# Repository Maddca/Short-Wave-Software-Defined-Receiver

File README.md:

# Short-Wave-Software-Defined-Receiver
The goal of this project has been to design a Software Defined Radio Receiver with [Taylor Smith](https://github.com/TaylorSmith28) for the Engineering Electronics II class.
## Design Objectives
For this project we were given the following design objectives by [Dr. Rob Frohne](https://github.com/frohro):

#### Objectives
 - Low noise figure
 - Good image rejection
 - Minimum discernible signal of less than 1uV
 - $25 Budget

For specifications we originally were going to have a narrow bandpass filter, but ended up switching to a relatively wider one in the later stages of the project.

#### Specifications
 - Frequency Range of 7-12MHz
 - Short Wave Radio
 - Uses a Tayloe Mixer
 - Uses a Multiple Feedback Lowpass Filter and Amplifier
 	- 25 V/V gain with Cutoff Frequency of more than 50KHz
 - Butterworth Bandpass Filter
 - Uses the Raspberry Pi Pico
 
 ## Overview
 The SDR receiver connects to an antenna and filters, mixes, and amplifies that signal to achieve the desired I and Q signals. The I and Q signals are then sent through an external sound card with a sample rate of 48kHz where software then handles the demodulation of the signal into audio. The mixer requires a 90 degree offset of two clocks operating at a frequency that can be controlled through software. In our design we use a Raspberry Pi Pico to control an si5351 to supply those two 90 degree offset clocks. There were some significant issues with this since the code supplied by professor Frohne didn't work when ported over to the Raspberry Pi Pico. In theory though the Raspberry Pi Pico interfaces with Quisk to tune to a certain frequency by adjusting the frequency of the si5351 clocks.
 
 ## Theory

The Block Diagram above shows the basics of how the SDR works. We get an input signal from the antenna which is passed through the bandpass filter and sent to the Tayloe Mixer that uses a 1:4 demultiplexer and low pass filters and ampliers to create the I and Q quardrature signals. After the demuiltiplexer creates 4 signals each 90 degrees out of phase with each other those signals are combined together to create the I and Q signals to be sent to the Audio Jack.

## Schematic Version 6

### Bandpass Filter

 Above is the bandpass filter made using the [LC Filter Design Tool](https://rf-tools.com/lc-filter/.). It is a 3rd order, conventional series first, Butterworth, bandpass filter that passes 7-12Mhz frequencies.
 
 ### Tayloe Mixer
 
The Tayloe Mixer above is comprised of the Demultiplexer stage which seperates the input signal into four signals all 90 degrees out of phase with each other. Then the signals that are 180 degrees out of phase with each other are combined in the following amplifier and low pass filter stage using opamps. The filter/amplifier here is a multiple feedback low pass filter and amplifier, in this case multiple refers to the filter being second order rather than single order.

### Voltage Smoother

The voltage smoother above simply uses varying capacitor sizes to lower the noise coming from the USB.

### Oscillator

The oscillator above is what outputs the clock signals necessary to run the Tayloe Mixer. It is controlled by the Raspberry Pi Pico on the SDA and SCL inputs.

### Raspberry Pi Pico

Above is the part of the schematic dealing with the Raspberry Pi Pico. The main thing of interest here is to note the pull up resistors and the GPIO pin the SDA and SCL are connected to, since the pin needs to be I2C compatible, in this case pins 6 and 7 or GPIO 4 and 5 are I2C compatible.

## Simulations
Simulations were for the most part conducted in [LTSpice](https://www.analog.com/en/design-center/design-tools-and-calculators/ltspice-simulator.html).
### Bandpass Filter Simulations

The Bandpass filter was designed to pass frequencies between 7 and 12 MHz, which is what the ac simulation shows.

### Lowpass Filter Simulations

## Issues
The first major issue we encountered was not having functional code because of the port over to Raspberry Pi Pico. It took 2 days of troubleshooting to get the appropriate clock signal to display and thats still without the ability to change frequencies, which currently causes the program to hang. The second major issue was much simpler. When we went to test our bandpass filter we came to the realization that one of the leads on the handwound inductors couldn't make a good connection because there was still enamel on it. After several failed attempts to remove it we decided jump the bandpass filter, but much later discovered that shorting the bandpass filter with a wire caused one of the resistors responsible for the dc offset to be in parallel with the resistor in the signal generator. This caused us to lose our DC Offset which caused the SDR not to work. To resolve this issue we simply shorted the bandpass filter with a capacitor.
## Results
We ended up with a minimum discernable signal of approx 1uV and when we tried the antenna we listened to some Catholic sermon on sunday.

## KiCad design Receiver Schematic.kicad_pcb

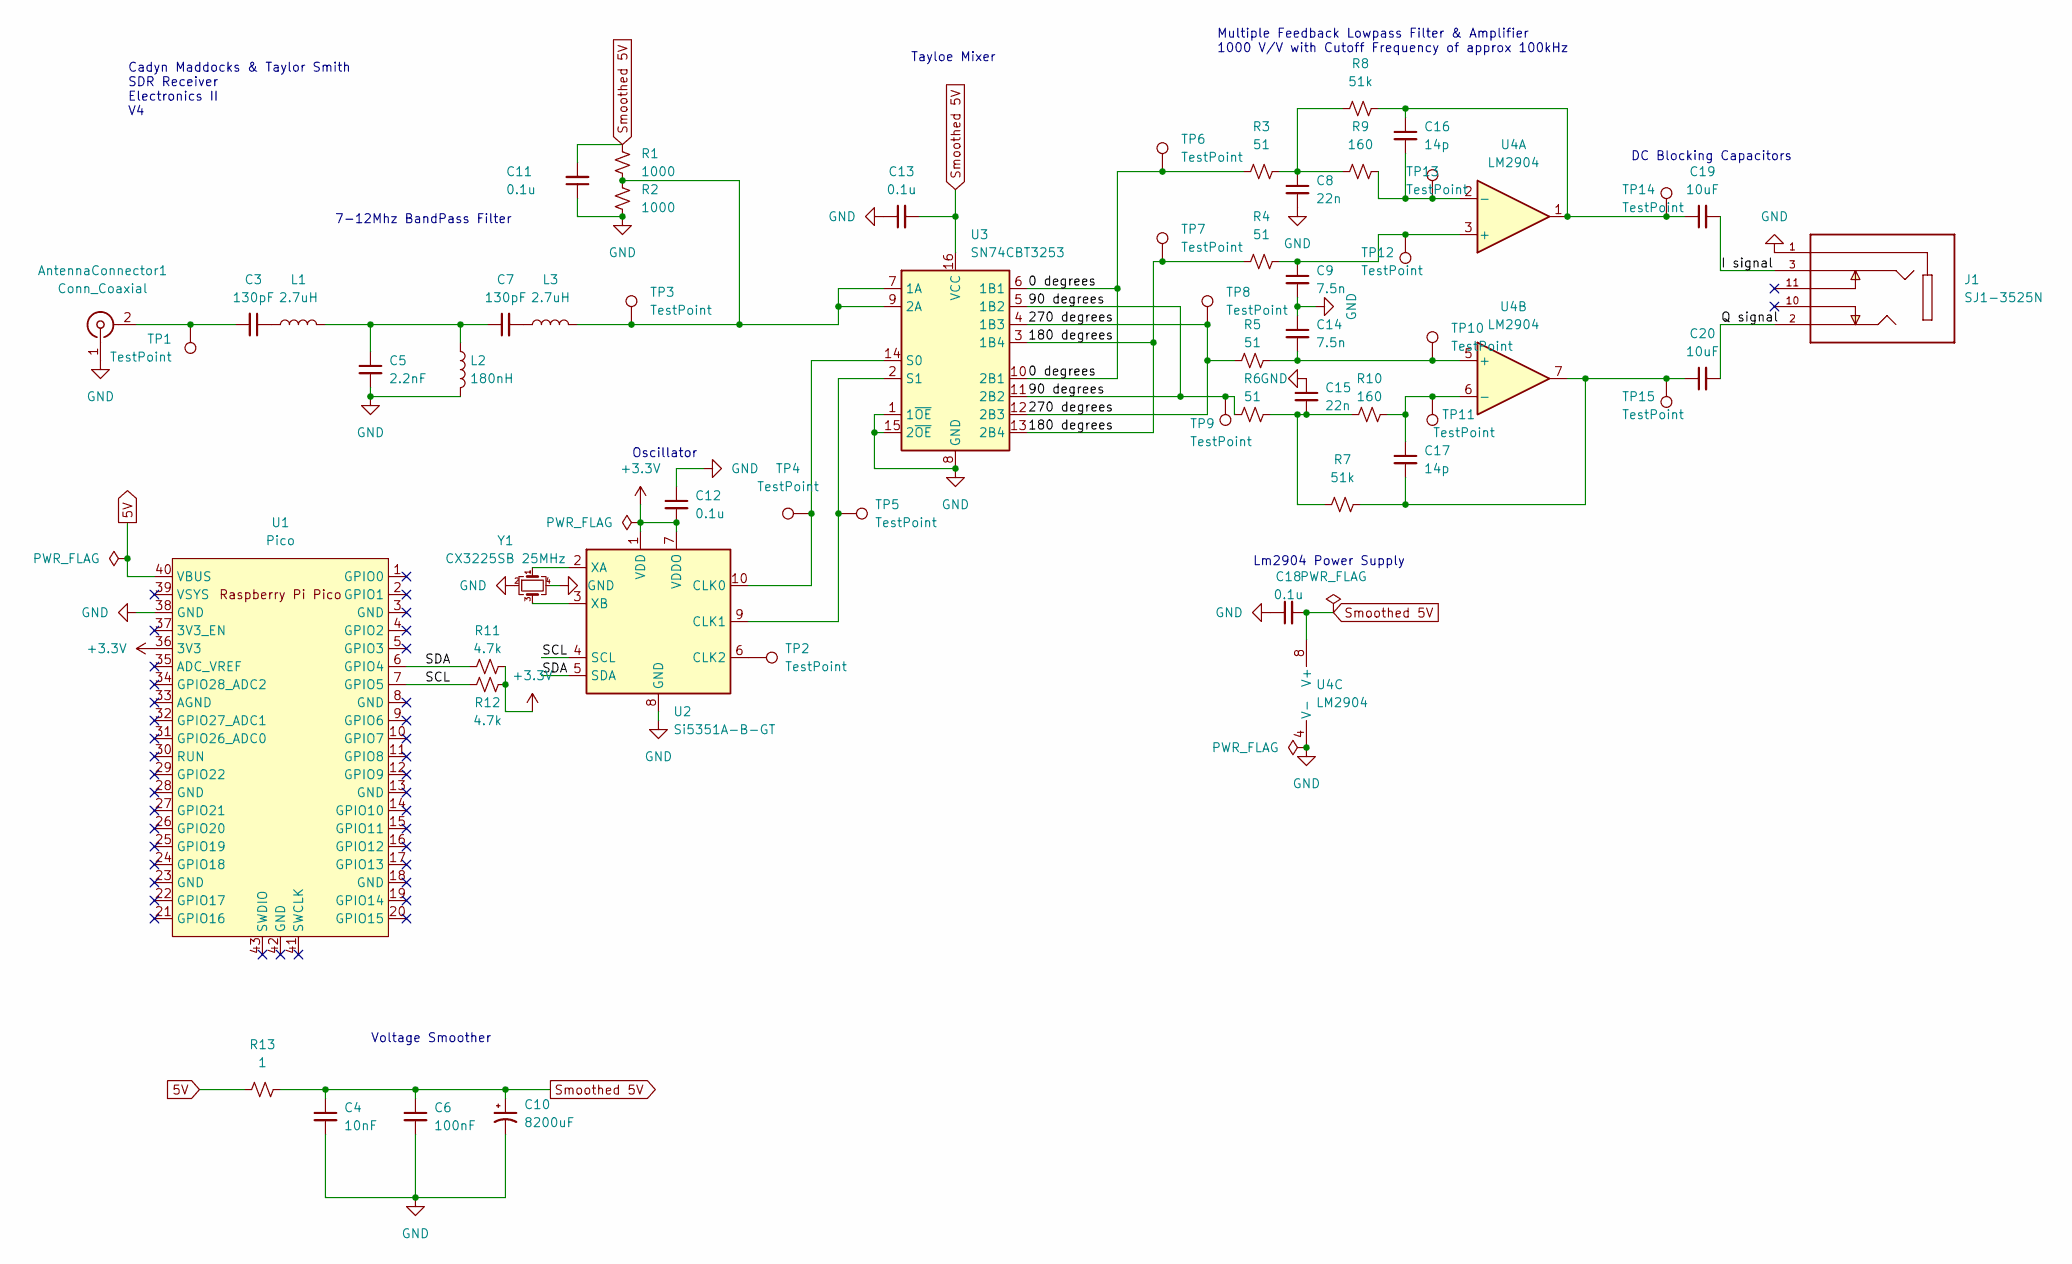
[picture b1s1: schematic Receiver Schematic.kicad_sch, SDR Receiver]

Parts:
AntennaConnector1: Conn_Coaxial; BNC_Amphenol_B6252HB-NPP3G-50_Horizontal
C3, C7: 130pF; C_0805_2012Metric
C4: 10nF; C_0805_2012Metric
C5: 2.2nF; C_0805_2012Metric
C6: 100nF; C_0805_2012Metric
C8, C15: 22n; C_0805_2012Metric
C9: 7.5n; C_0805_2012Metric
C10: 8200uF; CP_Radial_D16.0mm_P7.50mm
C11, C12, C13, C18: 0.1u; C_0805_2012Metric
C14: 7.5n; C_1206_3216Metric
C16, C17: 14p; C_0805_2012Metric
C19, C20: 10uF; C_0805_2012Metric
J1: SJ1-3525N; CUI_SJ1-3525N; PARTREV 1.02
L1, L3: 2.7uH; L_Toroid_Vertical_L10.0mm_W5.0mm_P5.08mm
L2: 180nH; L_Toroid_Vertical_L10.0mm_W5.0mm_P5.08mm
R1, R2: 1000; R_0805_2012Metric
R3, R4, R5, R6: 51; R_0805_2012Metric
R7, R8: 51k; R_0805_2012Metric
R9, R10: 160; R_0805_2012Metric
R11, R12: 4.7k; R_0805_2012Metric
R13: 1; R_0805_2012Metric
TP1, TP2, TP3, TP4, TP5, TP6, TP7, TP8, TP9, TP10, TP11, TP12, TP13, TP14, TP15: TestPoint; TestPoint_THTPad_2.0x2.0mm_Drill1.0mm
U1: Pico; RPi_Pico_SMD_TH
U2: Si5351A-B-GT; MSOP-10_3x3mm_P0.5mm
U3: SN74CBT3253; SOIC-16_3.9x9.9mm_P1.27mm
U4: LM2904; SOIC-8_3.9x4.9mm_P1.27mm
Y1: CX3225SB 25MHz; Crystal_SMD_TXC_7M-4Pin_3.2x2.5mm

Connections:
5V: R13.1, U1.40 (VBUS)
+3V3: C12.2, R11.2, R12.2, U1.36 (3V3), U2.1 (VDD), U2.7 (VDDO)
/0 degrees: R3.1, TP6.1, U3.6 (1B1), U3.10 (2B1)
/90 degrees: R6.1, TP9.1, U3.5 (1B2), U3.11 (2B2)
/180 degrees: R4.1, TP7.1, U3.3 (1B4), U3.13 (2B4)
/270 degrees: R5.1, TP8.1, U3.4 (1B3), U3.12 (2B3)
/I signal: C19.2, J1.3
/Q signal: C20.2, J1.2
/SCL: R12.1, U1.7 (GPIO5), U2.4 (SCL)
/SDA: R11.1, U1.6 (GPIO4), U2.5 (SDA)
GND: AntennaConnector1.1 (In), C4.2, C5.2, C6.2, C8.2, C9.2, C10.2, C11.1, C12.1, C13.1, C14.1, C15.1, C18.1, J1.1, L2.2, R2.2, U1.38 (GND), U2.8 (GND), U3.1 (1~OE), U3.8 (GND), U3.15 (2~OE), U4.4 (V-), Y1.2, Y1.4
unnamed: AntennaConnector1.2 (Ext), C3.2, TP1.1
unnamed: C3.1, L1.1
unnamed: C5.1, C7.1, L1.2, L2.1
unnamed: C7.2, L3.1
unnamed: C8.1, R3.2, R8.1, R9.1
unnamed: C9.1, R4.2, TP12.1, U4.3 (+)
unnamed: C14.2, R5.2, TP10.1, U4.5 (+)
unnamed: C15.2, R6.2, R7.1, R10.1
unnamed: C16.1, C19.1, R8.2, TP14.1, U4.1
unnamed: C16.2, R9.2, TP13.1, U4.2 (-)
unnamed: C17.1, R10.2, TP11.1, U4.6 (-)
unnamed: C17.2, C20.1, R7.2, TP15.1, U4.7
unnamed: L3.2, R1.2, R2.1, TP3.1, U3.7 (1A), U3.9 (2A)
unnamed: TP2.1, U2.6 (CLK2)
unnamed: TP4.1, U2.10 (CLK0), U3.14 (S0)
unnamed: TP5.1, U2.9 (CLK1), U3.2 (S1)
unnamed: U2.2 (XA), Y1.1
unnamed: U2.3 (XB), Y1.3
Smoothed 5V: C4.1, C6.1, C10.1, C11.2, C13.2, C18.2, R1.1, R13.2, U3.16 (VCC), U4.8 (V+)

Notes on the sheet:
Multiple Feedback Lowpass Filter & Amplifier 1000 V/V with Cutoff Frequency of approx 100kHz
Oscillator
Lm2904 Power Supply
Tayloe Mixer
7-12Mhz BandPass Filter
DC Blocking Capacitors
Voltage Smoother
Cadyn Maddocks & Taylor Smith SDR Receiver Electronics II V4

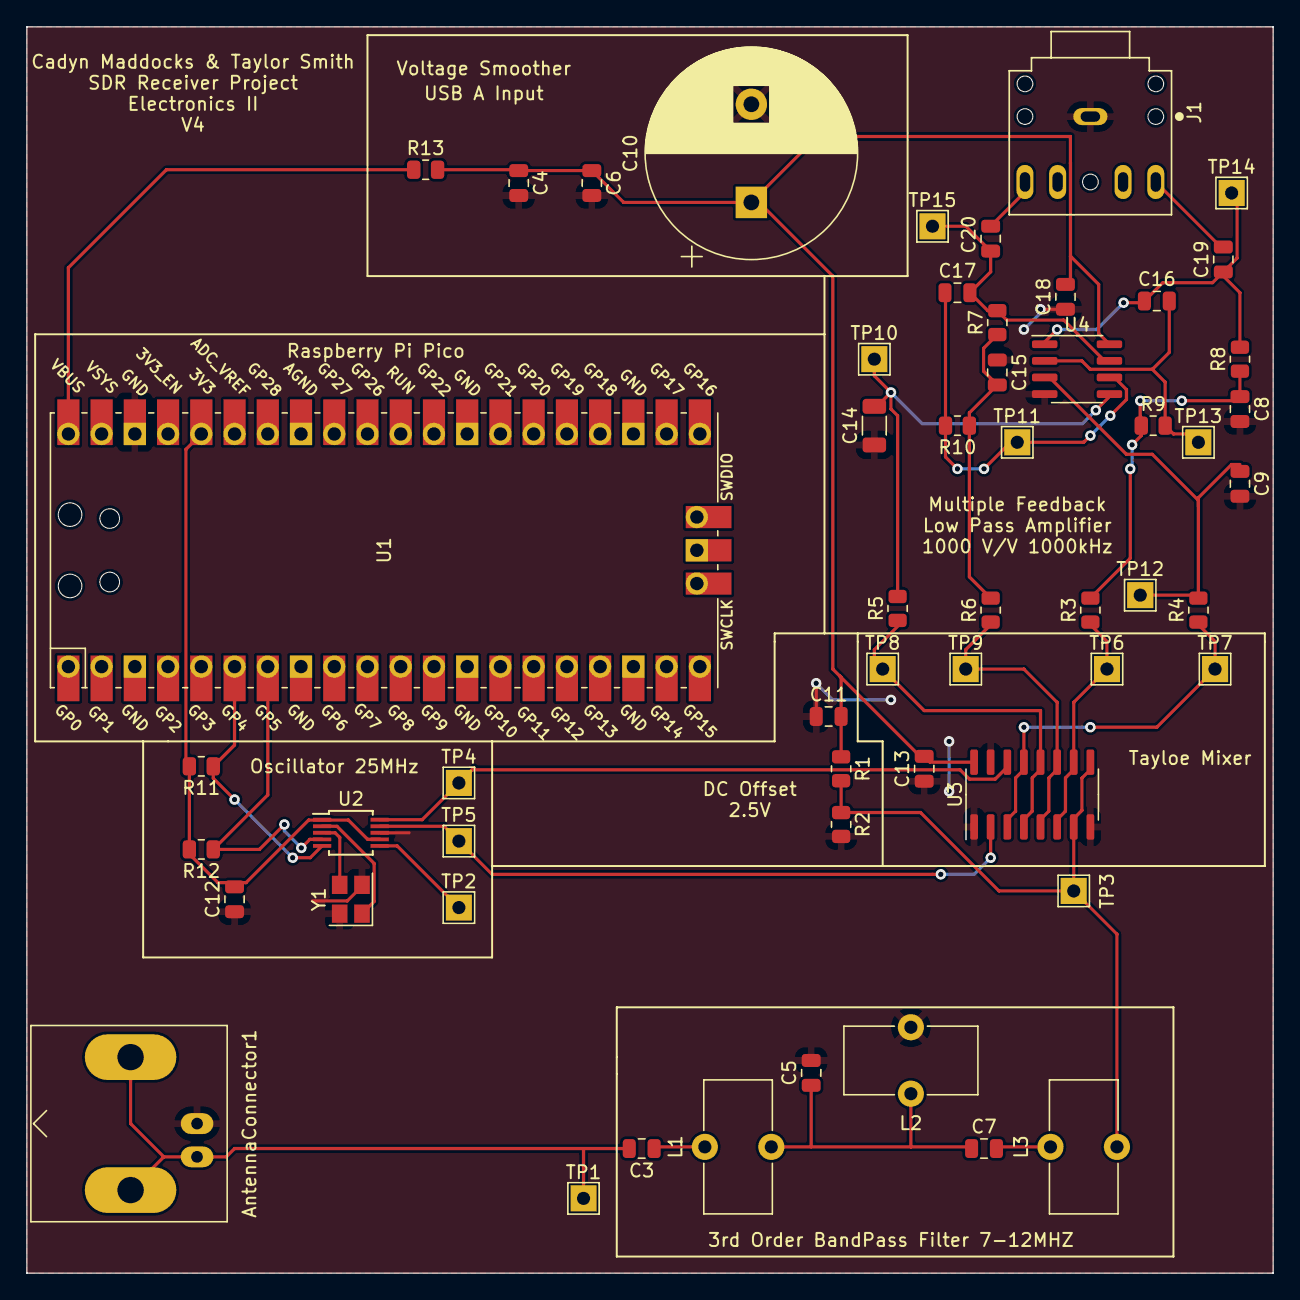
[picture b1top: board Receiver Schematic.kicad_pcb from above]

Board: 2 copper layers, 95.3 x 95.2 mm, 56 parts (0 on the bottom side), 30 nets.

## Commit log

2022-04-28 Receiver Schematic V1
    The first version of the quadrature sampling downconversion software defined receiver uploaded to the GitHub project page.
2022-04-28 First version with a pcb
    V3
2022-04-29 V4
    V4
2022-04-29 LTSpice Simulations
    Some of the LTSpice Simulations
2022-06-06 Version 5
    Updated File organization and minor fixes.
2022-06-06 Further Updated schematic to resemble current board layout
2022-06-07 Final Schematic/PCB version
    Version 6 of the SDR Design
2022-06-07 Started Work on Readme
2022-06-07 Block Diagram Upload
2022-06-07 Added Bandpass filter simulation
2022-06-07 Adding Images
2022-06-07 Changed file type of Frequency Test
2022-06-07 Please work
2022-06-07 Changed File type
